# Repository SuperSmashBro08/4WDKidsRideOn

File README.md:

# ESP32 ↔ Teensy 4.1 OTA Workflow

This repository contains two coordinated sketches that allow an ESP32-S3 to deliver over-the-air
(OTA) firmware updates to a Teensy 4.1-based TNC. The ESP32 hosts a small web page where you upload
the Intel HEX file exported by the Arduino IDE. The Teensy runs a purpose-built stub that
handshakes with the ESP32, receives the HEX records, writes them directly into its internal QSPI
flash, and automatically reboots into the freshly programmed image.

The sections below walk through every step from wiring to flashing.

## Hardware overview

* **Teensy 4.1** running the OTA stub sketch found under `firmware/Teensy41_Target/teensystub`.
* **ESP32-S3** running the uploader sketch in `firmware/ESP32_Uploader/esp32_uploader`.
* **Serial link** – connect ESP32 GPIO43 → Teensy RX2 (pin 7) and ESP32 GPIO44 ← Teensy TX2 (pin 8).
  Share ground between the boards. Keep the wiring short (<15 cm) for clean 115200 baud links.
* **Optional debug USB** – connect the Teensy micro‑USB to a computer to monitor verbose logs while
  testing. The ESP32 USB serial console is also helpful for Wi‑Fi and OTA diagnostics.

## Preparing the firmware

1. Open the Teensy project you want to deploy in the Arduino IDE and select **Teensy 4.1** as the
   target board.
2. Use **Sketch → Export compiled Binary**. This generates a `.hex` file in the sketch folder.
3. (Optional) Rename the HEX file with the build date or version so you can identify it easily on
the ESP32 upload page.

## Building and loading the OTA stub

1. In the Arduino IDE open `firmware/Teensy41_Target/teensystub/teensystub.ino`.
2. Verify that the `OTA_TOKEN` matches the value in `firmware/ESP32_Uploader/esp32_uploader/secrets.h`.
   Changing the token requires reflashing **both** boards.
3. Click **Upload** to flash the stub onto the Teensy 4.1. The stub prints its firmware version and
   provides a small serial console (commands: `help`, `status`, `version`, `reboot`).
4. Leave the stub in place. Every subsequent OTA update will completely replace it with your real
   TNC firmware, so be sure to keep a copy handy if you ever need to revert.

## Flashing workflow (ESP32 as the OTA server)

1. Flash the ESP32 with `firmware/ESP32_Uploader/esp32_uploader.ino`, update Wi‑Fi credentials in
   `secrets.h`, and allow it to join your network. The serial console prints the IP address and the
   optional mDNS hostname (`esp32-teensy.local`).
2. Visit `http://<esp32-ip>/` in a browser. The page exposes a single file upload form.
3. Click **Choose File**, select the Teensy `.hex` binary, and press **Upload & Flash**.
4. The ESP32 performs the following automatically:
   * Opens the serial link to the Teensy and sends `HELLO <token>`.
   * Streams each Intel HEX record line-by-line (`BEGIN HEX`, `L …`, `END`).
   * Displays a live log containing acknowledgements for every line.
5. The Teensy stub validates every record, accumulates data into 4 KB sectors, erases/programs its
   internal flash, and acknowledges each line with `OK <n>`. When the last record arrives it sends a
   summary (`HEX OK …`) followed by `APPLIED`, waits one second, and triggers a software reset to
   boot into the newly flashed firmware.
6. The ESP32 page updates with a success message showing transfer statistics. If anything fails you
   will see the Teensy-provided error reason (checksum mismatch, unsupported record type, flash
   write failure, missing EOF, etc.).

## Recovery and troubleshooting

* If the Teensy reports `HEX FAIL` immediately after `BEGIN HEX`, ensure the `OTA_TOKEN` matches and
  that both boards are wired correctly. Any lingering serial data from previous runs should be
  cleared by resetting the Teensy.
* When a transfer aborts mid-stream, the Teensy keeps the original firmware. The stub only commits
  data after successfully writing each 4 KB sector and it does not reset until the entire image
  passes validation.
* To recover the stub after flashing a faulty firmware, press and hold the Teensy **Program** button
  and upload the stub again from the Arduino IDE via USB. Once the stub is running you can retry the
  OTA process.
* Use the Teensy USB console command `status` to inspect how many lines, bytes, sectors, and pages
  were processed in the most recent session. This mirrors the data returned to the ESP32 uploader.

## Safety notes

* The stub only accepts data inside the Teensy 4.1 flash address window (`0x6000_0000 – 0x6020_0000`).
  Any record outside that range is rejected before any sector is erased.
* Flash programming runs with interrupts temporarily disabled while a page is written. The LED on
  pin 13 continues to heartbeat so you can see the board is alive during a long update.
* After a successful OTA the stub reboots automatically. No additional hardware toggling of the
  Program pin is required.

With the steps above the entire flow—uploading the HEX file, streaming it to the Teensy, flashing,
and rebooting—happens end-to-end without manual intervention.

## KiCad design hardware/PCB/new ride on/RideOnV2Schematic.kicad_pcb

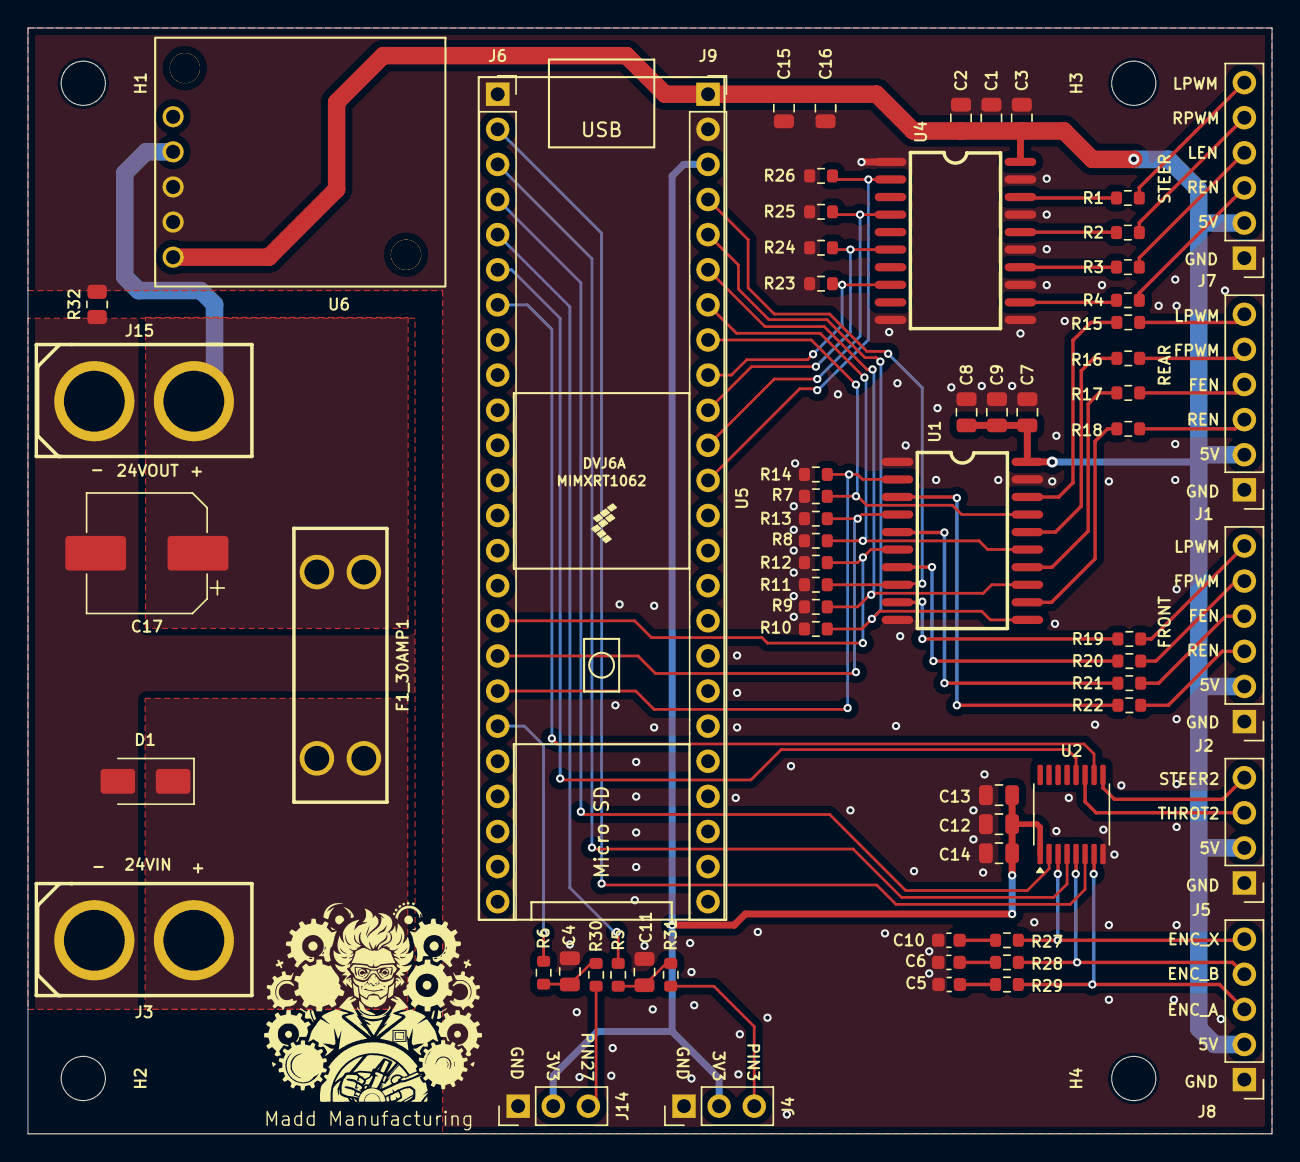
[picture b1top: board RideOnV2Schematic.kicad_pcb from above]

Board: 2 copper layers, 90.0 x 80.0 mm, 71 parts (0 on the bottom side), 61 nets.

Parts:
C1, C4, C7, C11, C12, C15: 100nF; C_0805_2012Metric
C2, C8, C13: 1uF; C_0805_2012Metric
C3, C9, C14: 10uF; C_0805_2012Metric
C5, C6, C10: 100pF; C_0603_1608Metric
C16: 4.7uF; C_0805_2012Metric
C17: 220uF/35V; CP_Elec_8x10.5
D1: SMAJ33A; D_SMA
F1_30AMP1: Fuse; FUSE-TH_4P-L19.8-W6.7_3557-2
H1, H2, H3, H4: MountingHole; MountingHole_3.2mm_M3
J1, J2, J7: Conn_01x06; PinHeader_1x06_P2.54mm_Vertical
J3, J15: XT60-M.; CONN-TH_XT60
J4, J14: Conn_01x03; PinHeader_1x03_P2.54mm_Vertical
J5: Conn_01x04; PinHeader_1x04_P2.54mm_Vertical
J6, J9: Conn_01x24; PinSocket_1x24_P2.54mm_Vertical
J8: Conn_01x05; PinHeader_1x05_P2.54mm_Vertical
R1, R2, R3, R4, R5, R6, R15, R16, R17, R18, R19, R20, R21, R22: 33R; R_0603_1608Metric
R7, R8, R9, R10, R11, R12, R13, R14, R23, R24, R25, R26: 10k; R_0603_1608Metric
R27, R28, R29, R30, R31: 100R; R_0603_1608Metric
R32: 0R; R_0805_2012Metric
U1, U4: SN74AHCT244; SOIC-20_L12.8-W7.5-P1.27-LS10.3-BL
U2: CD74HC4050; TSSOP-16_4.4x5mm_P0.65mm
U5: Teensy4.1; Teensy41
U6: D24V50F5

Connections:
+3.3V: C12.1, C13.1, C14.1, J4.2, J9.3, J14.2, U2.1 (VCC)
+5V: C1.1, C2.1, C3.1, C7.1, C8.1, C9.1, C15.2, C16.2, J1.2, J2.2, J5.2, J7.2, J8.2, J9.1, U1.20 (VCC), U4.20 (VCC), U6.5 (VOUT)
+24V: C17.1, F1_30AMP1.1, J15.2, U6.2 (VIN)
/24VIN: D1.1 (A1), F1_30AMP1.2, J3.2
/PIN_0: J6.2, U2.6
/PIN_1: J6.3, U2.4
/PIN_2: J6.4, U2.2
/PIN_3: C11.1, R5.1, R31.1
/PIN_4: J6.6, U2.12
/PIN_5: J6.7, U2.10
/PIN_15: J9.12, R26.1, U4.2 (1A1)
/PIN_16: J9.11, R25.1, U4.4 (1A2)
/PIN_17: J9.10, R24.1, U4.6 (1A3)
/PIN_18: J9.9, R23.1, U4.8 (1A4)
/PIN_19: J9.8, R7.1, U1.17 (2A4)
/PIN_20: J9.7, R8.1, U1.15 (2A3)
/PIN_21: J9.6, R9.1, U1.13 (2A2)
/PIN_22: J9.5, R10.1, U1.11 (2A1)
/PIN_23: J9.4, R11.1, U1.8 (1A4)
/PIN_24: J6.16, R12.1, U1.6 (1A3)
/PIN_25: J6.17, R13.1, U1.4 (1A2)
/PIN_26: J6.18, R14.1, U1.2 (1A1)
/PIN_27: C4.1, R6.1, R30.1
/PIN_ENC_A: J8.3, R29.2, U2.7
/PIN_ENC_B: J8.4, R28.2, U2.5
/PIN_ENC_X: J8.5, R27.2, U2.3
/PIN_FRONT_FEN: J2.4, R21.2
/PIN_FRONT_FPWM: J2.5, R20.2
/PIN_FRONT_REN: J2.3, R22.2
/PIN_FRONT_RPWM: J2.6, R19.2
/PIN_REAR_FEN: J1.4, R17.2
/PIN_REAR_FPWM: J1.5, R16.2
/PIN_REAR_REN: J1.3, R18.2
/PIN_REAR_RPWM: J1.6, R15.2
/PIN_STEERING2: J5.4, U2.9
/PIN_STEER_LEN: J7.4, R3.2
/PIN_STEER_LPWM: J7.6, R1.2
/PIN_STEER_REN: J7.3, R4.2
/PIN_STEER_RPWM: J7.5, R2.2
/PIN_THROTTLE2: J5.3, U2.11
GND: C1.2, C2.2, C3.2, C4.2, C5.2, C6.2, C7.2, C8.2, C9.2, C10.2, C11.2, C12.2, C13.2, C14.2, C15.1, C16.1, J1.1, J2.1, J4.1, J5.1, J6.1, J7.1, J8.1, J9.2, J14.1, R7.2, R8.2, R9.2, R10.2, R11.2, R12.2, R13.2, R14.2, R23.2, R24.2, R25.2, R26.2, R32.2, U1.1 (1OE), U1.10 (GND), U1.19 (2OE), U2.8 (GND), U4.1 (1OE), U4.10 (GND), U4.11 (2A1), U4.13 (2A2), U4.15 (2A3), U4.17 (2A4), U4.19 (2OE), U6.3 (GND1), U6.4 (GND2)
GNDPWR: C17.2, D1.2 (A2), J3.1, J15.1, R32.1
unnamed: C5.1, R29.1
unnamed: C6.1, R28.1
unnamed: C10.1, R27.1
unnamed: J4.3, R31.2
unnamed: J6.5, R5.2
unnamed: J6.19, R6.2
unnamed: J14.3, R30.2
unnamed: R15.1, U1.18 (1Y1)
unnamed: R16.1, U1.16 (1Y2)
unnamed: R17.1, U1.14 (1Y3)
unnamed: R18.1, U1.12 (1Y4)
unnamed: R19.1, U1.9 (2Y1)
unnamed: R20.1, U1.7 (2Y2)
unnamed: R21.1, U1.5 (2Y3)
unnamed: R22.1, U1.3 (2Y4)
unnamed: R1.1, U4.18 (1Y1)
unnamed: R2.1, U4.16 (1Y2)
unnamed: R3.1, U4.14 (1Y3)
unnamed: R4.1, U4.12 (1Y4)

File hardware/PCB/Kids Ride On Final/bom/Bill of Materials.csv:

"Reference","Qty","Value","DNP","Footprint","MPN","LCSC"
"C1,C4,C7,C11,C12,C15","6","100nF","","Capacitor_SMD:C_0805_2012Metric","CC0805KRX7R9BB104","C49678"
"C2,C8,C13","3","1uF","","Capacitor_SMD:C_0805_2012Metric","CL21B105KBFNNNE","C28323"
"C3,C9,C14","3","10uF","","Capacitor_SMD:C_0805_2012Metric","CL21A106KAYNNNE","C15850"
"C5,C6,C10","3","100pF","DNP","Capacitor_SMD:C_0603_1608Metric","CL10C101JB8NNNC","C14858"
"C16","1","4.7uF","","Capacitor_SMD:C_0805_2012Metric","CL21A475KBQNNNE","C98192"
"C17","1","220uF/35V","","Capacitor_SMD:CP_Elec_8x10.5","HV1V227M0810PZ","C5246556"
"D1","1","SMAJ33A","","Diode_SMD:D_SMA","SMAJ33A","C353454"
"F1_30AMP1","1","Fuse","","Library:FUSE-TH_4P-L19.8-W6.7_3557-2","3557-2","C352820"
"H1,H2,H3,H4","4","MountingHole","","MountingHole:MountingHole_3.2mm_M3","DNP","DNP"
"J1,J2,J7","3","Conn_01x06","","Connector_PinHeader_2.54mm:PinHeader_1x06_P2.54mm_Vertical","PZ254V-11-06P","C492405"
"J3,J15","2","XT60-M.","","Library:CONN-TH_XT60","XT60-M.","C98733"
"J4,J14","2","Conn_01x03","","Connector_PinHeader_2.54mm:PinHeader_1x03_P2.54mm_Vertical","PZ254V-11-03P","C2937625"
"J5","1","Conn_01x04","","Connector_PinHeader_2.54mm:PinHeader_1x04_P2.54mm_Vertical","PZ254V-11-04P","C2691448"
"J6,J9","2","Conn_01x24","","Connector_PinSocket_2.54mm:PinSocket_1x24_P2.54mm_Vertical","X6511FV-24-C85D32","C2883741"
"J8","1","Conn_01x05","","Connector_PinHeader_2.54mm:PinHeader_1x05_P2.54mm_Vertical","PZ254V-11-05P","C492404"
"R1,R2,R3,R4,R5,R6,R15,R16,R17,R18,R19,R20,R21,R22","14","33R","","Resistor_SMD:R_0603_1608Metric","RC0603FR-0733RL","C108661"
"R7,R8,R9,R10,R11,R12,R13,R14,R23,R24,R25,R26","12","10k","","Resistor_SMD:R_0603_1608Metric","RC0603FR-0710KL","C98220"
"R27,R28,R29","3","100R","DNP","Resistor_SMD:R_0603_1608Metric","RC0603FR-07100RL","C105588"
"R30,R31","2","100R","","Resistor_SMD:R_0603_1608Metric","RC0603FR-07100RL","C105588"
"R32","1","0R","","Resistor_SMD:R_0805_2012Metric","RC0805FR-070RL","C100045"
"U1,U4","2","SN74AHCT244","","Library:SOIC-20_L12.8-W7.5-P1.27-LS10.3-BL","SN74AHCT244DWR","C2675568"
"U2","1","CD74HC4050","","Package_SO:TSSOP-16_4.4x5mm_P0.65mm","CD74HC4050PWR","C352825"
"U5","1","Teensy4.1","","Library:Teensy41","DNP","DNP"
"U6","1","D24V50F5","","Library:D24V50F5","DNP","DNP"

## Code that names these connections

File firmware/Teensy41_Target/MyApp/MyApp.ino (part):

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static constexpr uint8_t PIN_RC_T   = 5;   // RC throttle PWM in (T2)

// Steering BTS7960 (steer motor)
static constexpr uint8_t PIN_STEER_LPWM = 15;  // J7-6
static constexpr uint8_t PIN_STEER_RPWM = 16;  // J7-5
static constexpr uint8_t PIN_STEER_LEN  = 17;  // J7-4
static constexpr uint8_t PIN_STEER_REN  = 18;  // J7-3

// Drive motor outputs (M1 Front, M2 Rear)
// Front Motors (M1)
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  static const float KP_PWM_PER_DEG   = 6.0f;     // proportional gain

  // Use the global steering pins
  static const uint8_t PIN_MOT_LPWM = PIN_STEER_LPWM;  // 15
  static const uint8_t PIN_MOT_RPWM = PIN_STEER_RPWM;  // 16
  static const uint8_t PIN_MOT_LEN  = PIN_STEER_LEN;   // 17
  static const uint8_t PIN_MOT_REN  = PIN_STEER_REN;   // 18

  static const uint32_t STEER_PWM_FREQ = 20000; // 20 kHz
  static const int      PWM_MAX         = 255;   // 8-bit
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
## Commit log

2025-10-26 Implement transparent telnet bridge and quiet Teensy console
2025-10-26 Fix telnet double echo and stream handling
2025-10-26 Reject non-hex uploads in OTA web UI
2025-10-26 Improve OTA handshake diagnostics and feedback
2025-10-26 Simplify Teensy OTA pipeline
2025-10-27 Improve ESP32↔Teensy OTA handshake logging
2025-10-31 Add Teensy 4.1 OTA update loader
2025-10-31 Move OTA runtime into teensystub sketch
2025-10-31 Make Teensy OTA runtime Arduino-friendly
2025-10-31 Provide CMSIS fallback for Teensy OTA build
2025-10-31 Implement Teensy OTA flashing and update docs
2025-10-31 Add ESP32 OTA protocol support to FlasherX
2025-10-31 Main UPDATE!! OTA WORKING
2025-10-31 update1
2025-10-31 Update #2!!
2025-10-31 ESP32 UPDATE1!!
2025-11-01 MAIN UPDATE! VER 3
2025-11-01 Main!
2025-11-08 MAIN!!
2025-11-09 Backup Updated
2025-11-09 Improve Teensy console stability and add clear control
2025-11-09 Slow raw stream, faster UART, add telemetry
2025-11-09 Forward declare telemetry payload type
2025-11-09 Filter Teensy telemetry bytes during HELLO handshake
2025-11-09 Add include guard to OTA hub header
2025-11-09 Adjust ESP32 OTA hub include guard
2025-11-09 Restore OTA hub pragma once
2025-11-09 Remove duplicate telemetry parser definition
2025-11-09 Restore telemetry parser state reset
2025-11-09 Disable Teensy binary telemetry by default
2025-11-09 Fix Teensy console drain to preserve logs
2025-11-09 Declare conStore before use
2025-11-10 main Update
